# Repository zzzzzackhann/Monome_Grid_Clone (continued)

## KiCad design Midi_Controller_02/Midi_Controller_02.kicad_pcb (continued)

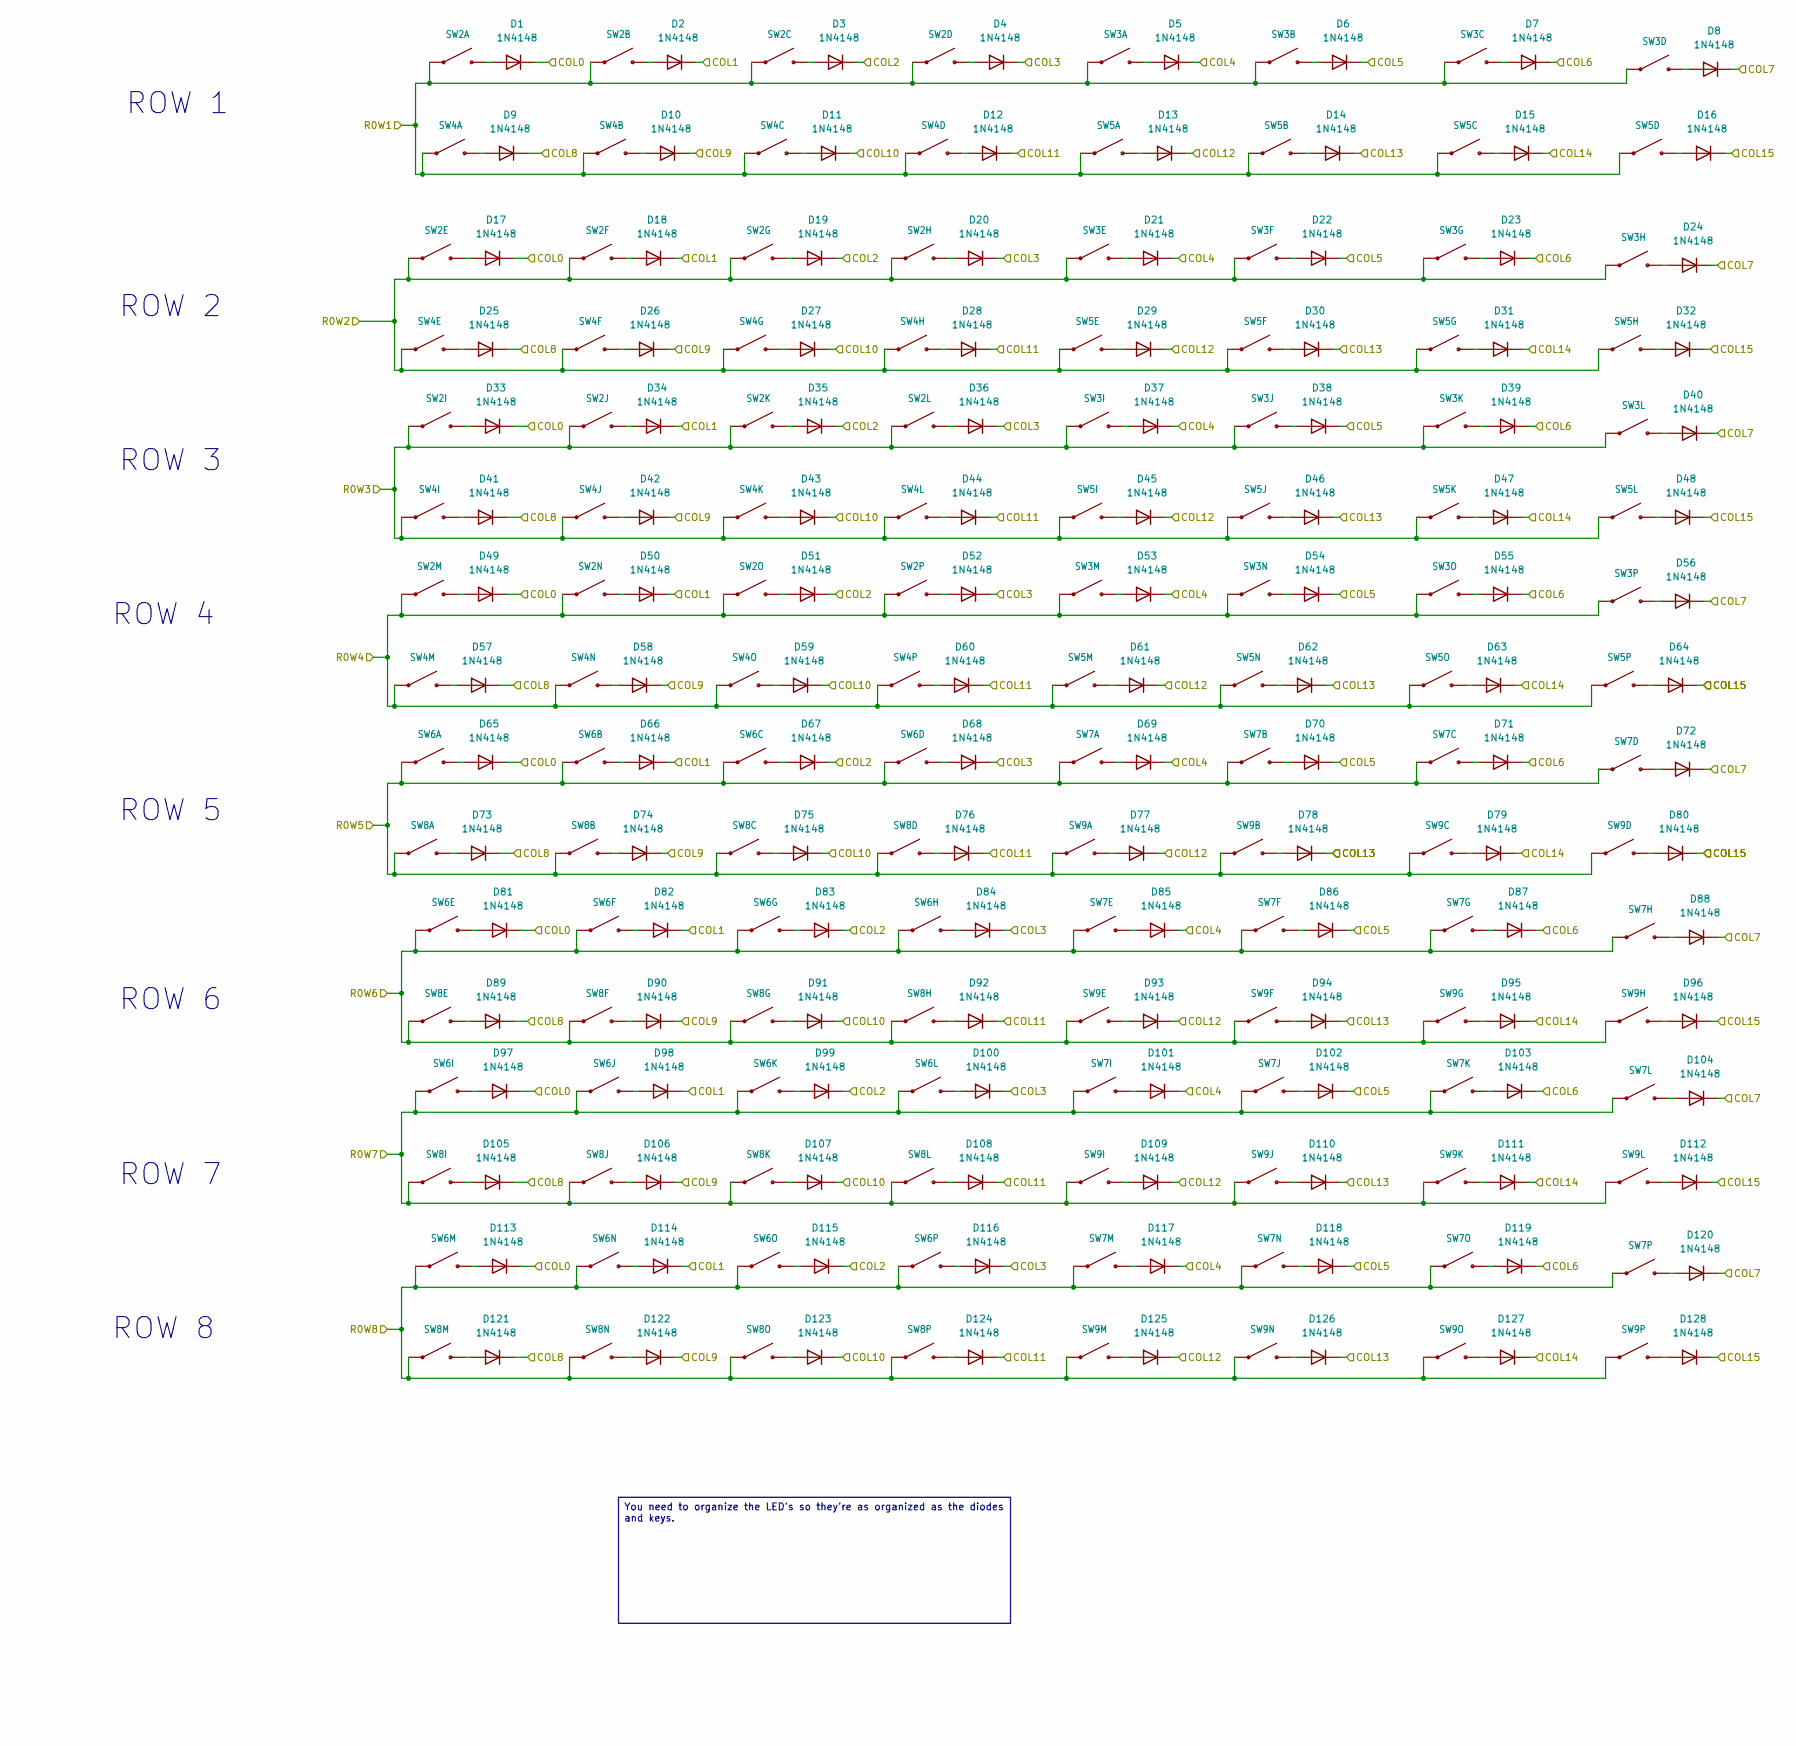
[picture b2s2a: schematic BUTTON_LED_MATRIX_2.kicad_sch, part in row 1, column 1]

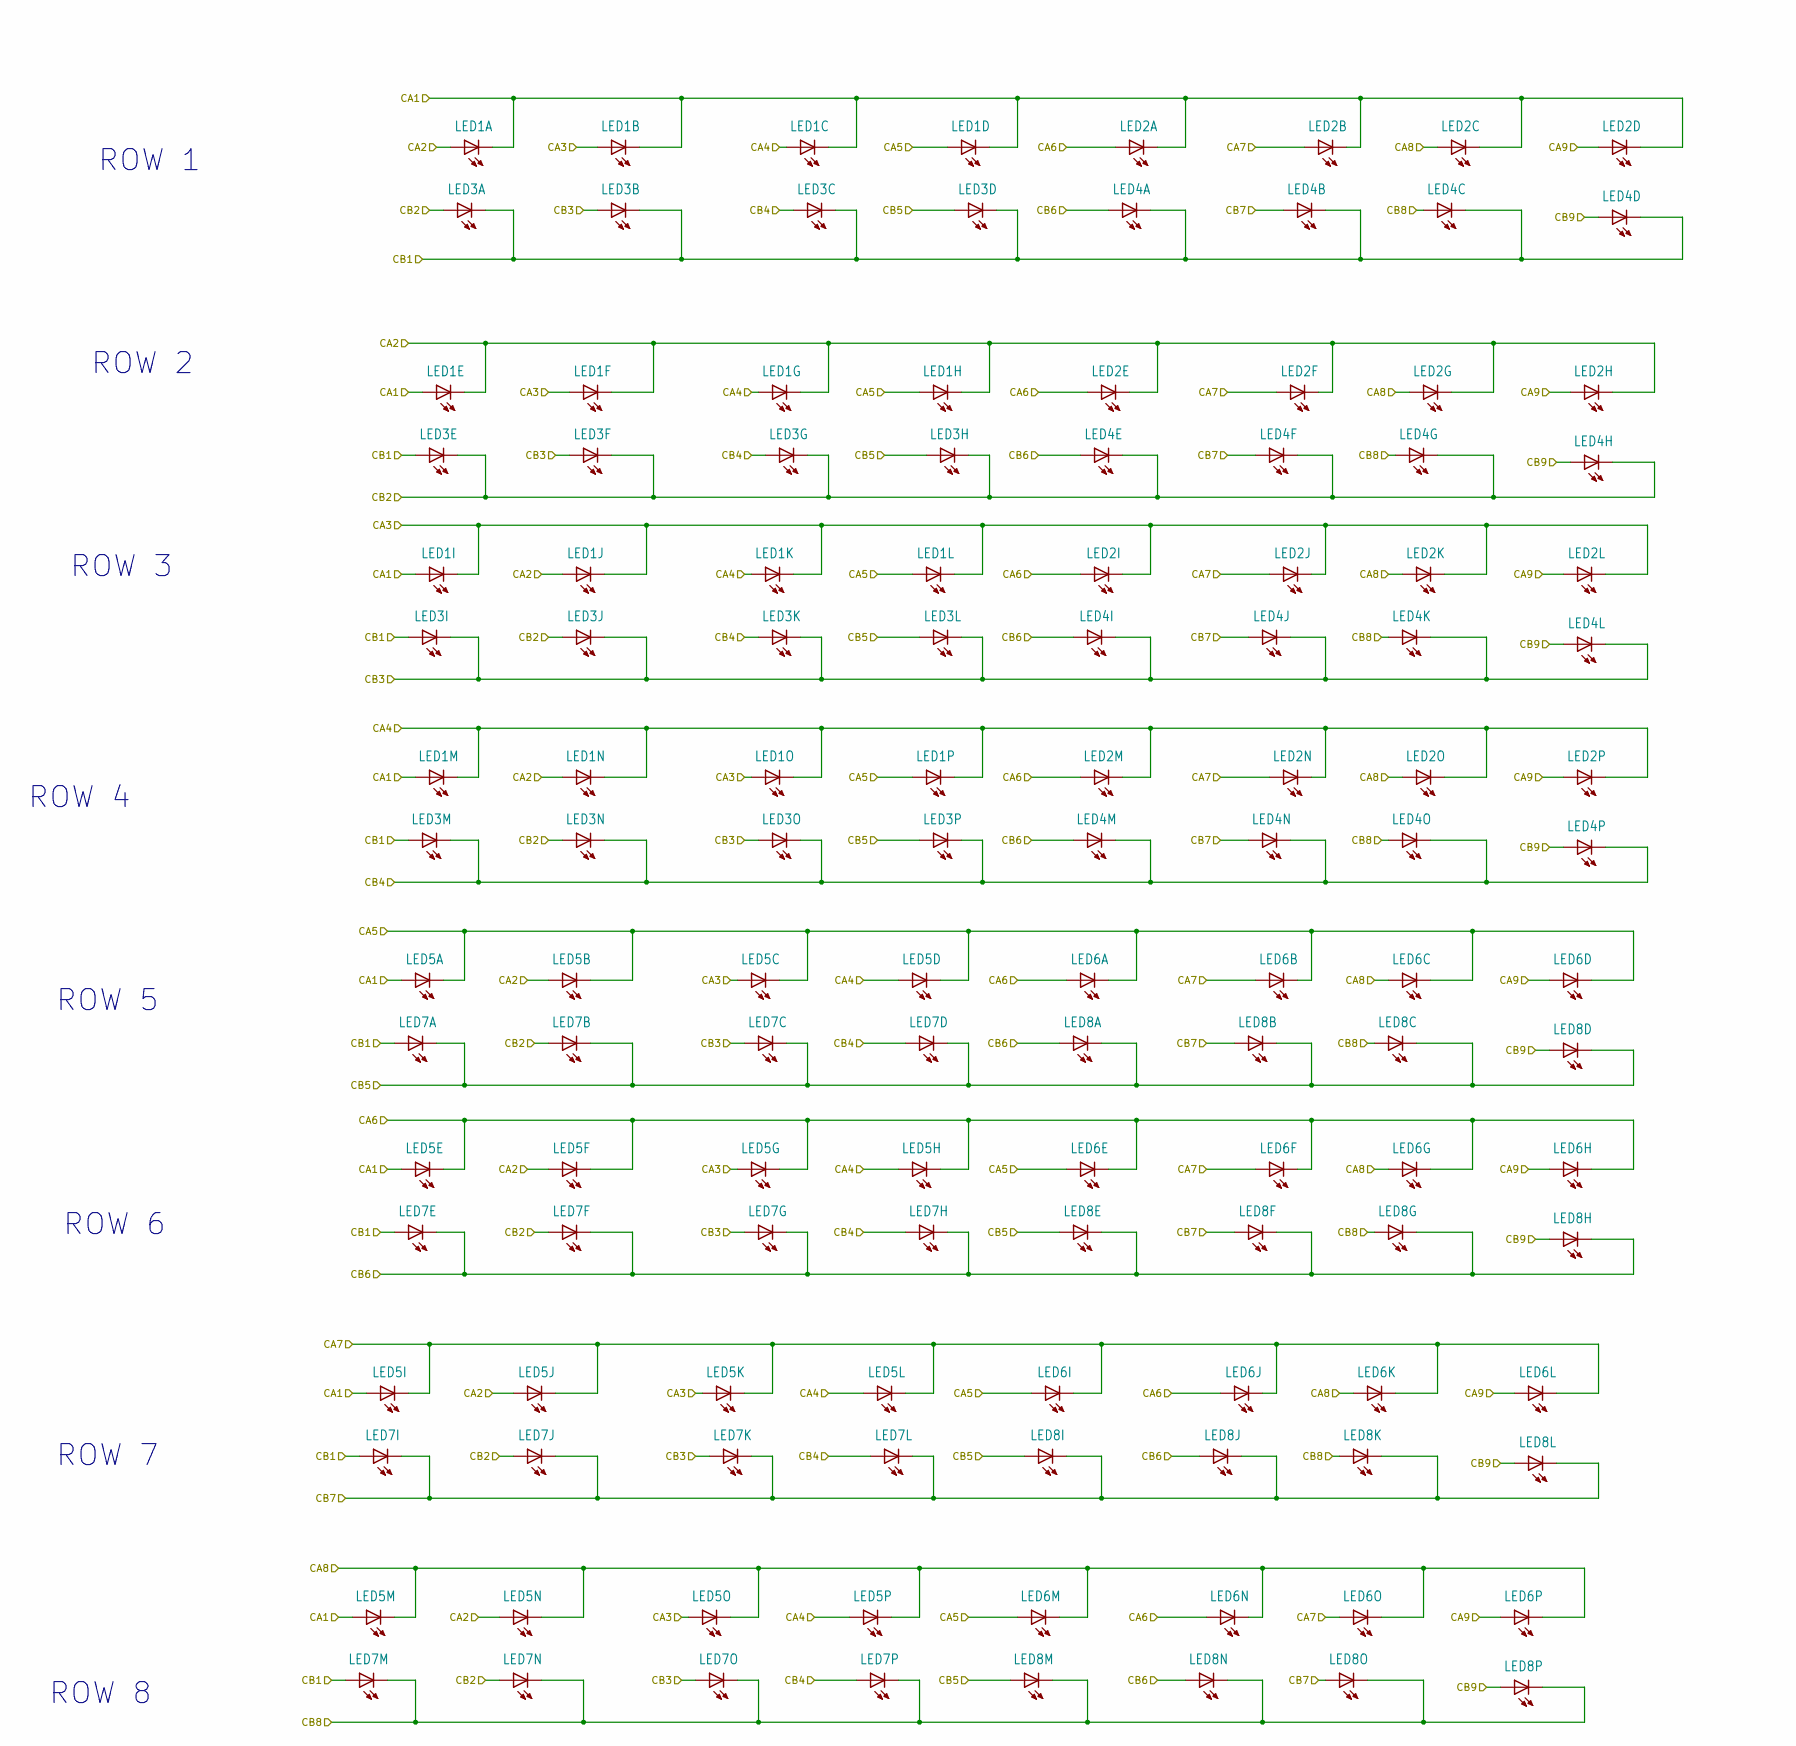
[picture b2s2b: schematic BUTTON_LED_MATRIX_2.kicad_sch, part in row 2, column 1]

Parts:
D1, D2, D3, D4, D5, D6, D7, D8, D9, D10, D11, D12, D13, D14, D15, D16, D17, D18, D19, D20, D21, D22, D23, D24, D25, D26, D27, D28, D29, D30, D31, D32, D33, D34, D35, D36, D37, D38, D39, D40, D41, D42, D43, D44, D45, D46, D47, D48, D49, D50, D51, D52, D53, D54, D55, D56, D57, D58, D59, D60, D61, D62, D63, D64, D65, D66, D67, D68, D69, D70, D71, D72, D73, D74, D75, D76, D77, D78, D79, D80, D81, D82, D83, D84, D85, D86, D87, D88, D89, D90, D91, D92, D93, D94, D95, D96, D97, D98, D99, D100, D101, D102, D103, D104, D105, D106, D107, D108, D109, D110, D111, D112, D113, D114, D115, D116, D117, D118, D119, D120, D121, D122, D123, D124, D125, D126, D127, D128: 1N4148; D_SOD-123
LED1, LED2, LED3, LED4, LED5, LED6, LED7, LED8: LED3MM-4X4GRID
SW2, SW3, SW4, SW5, SW6, SW7, SW8, SW9: ELAST_PAD_SQUARE_10MM_5.4MM_4X4GRID

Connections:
/CONTROLLER-MATRIX/CA1: LED1.A5 (A), LED1.A9 (A), LED1.A13 (A), LED1.K1 (C), LED1.K2 (C), LED1.K3 (C), LED1.K4 (C), LED2.K1 (C), LED2.K2 (C), LED2.K3 (C), LED2.K4 (C), LED5.A1 (A), LED5.A5 (A), LED5.A9 (A), LED5.A13 (A); also elsewhere on the board
/CONTROLLER-MATRIX/CA2: LED1.A1 (A), LED1.A10 (A), LED1.A14 (A), LED1.K5 (C), LED1.K6 (C), LED1.K7 (C), LED1.K8 (C), LED2.K5 (C), LED2.K6 (C), LED2.K7 (C), LED2.K8 (C), LED5.A2 (A), LED5.A6 (A), LED5.A10 (A), LED5.A14 (A); also elsewhere on the board
/CONTROLLER-MATRIX/CA3: LED1.A2 (A), LED1.A6 (A), LED1.A15 (A), LED1.K9 (C), LED1.K10 (C), LED1.K11 (C), LED1.K12 (C), LED2.K9 (C), LED2.K10 (C), LED2.K11 (C), LED2.K12 (C), LED5.A3 (A), LED5.A7 (A), LED5.A11 (A), LED5.A15 (A); also elsewhere on the board
/CONTROLLER-MATRIX/CA4: LED1.A3 (A), LED1.A7 (A), LED1.A11 (A), LED1.K13 (C), LED1.K14 (C), LED1.K15 (C), LED1.K16 (C), LED2.K13 (C), LED2.K14 (C), LED2.K15 (C), LED2.K16 (C), LED5.A4 (A), LED5.A8 (A), LED5.A12 (A), LED5.A16 (A); also elsewhere on the board
/CONTROLLER-MATRIX/CA5: LED1.A4 (A), LED1.A8 (A), LED1.A12 (A), LED1.A16 (A), LED5.K1 (C), LED5.K2 (C), LED5.K3 (C), LED5.K4 (C), LED6.A5 (A), LED6.A9 (A), LED6.A13 (A), LED6.K1 (C), LED6.K2 (C), LED6.K3 (C), LED6.K4 (C); also elsewhere on the board
/CONTROLLER-MATRIX/CA6: LED2.A1 (A), LED2.A5 (A), LED2.A9 (A), LED2.A13 (A), LED5.K5 (C), LED5.K6 (C), LED5.K7 (C), LED5.K8 (C), LED6.A1 (A), LED6.A10 (A), LED6.A14 (A), LED6.K5 (C), LED6.K6 (C), LED6.K7 (C), LED6.K8 (C); also elsewhere on the board
/CONTROLLER-MATRIX/CA7: LED2.A2 (A), LED2.A6 (A), LED2.A10 (A), LED2.A14 (A), LED5.K9 (C), LED5.K10 (C), LED5.K11 (C), LED5.K12 (C), LED6.A2 (A), LED6.A6 (A), LED6.A15 (A), LED6.K9 (C), LED6.K10 (C), LED6.K11 (C), LED6.K12 (C); also elsewhere on the board
/CONTROLLER-MATRIX/CA8: LED2.A3 (A), LED2.A7 (A), LED2.A11 (A), LED2.A15 (A), LED5.K13 (C), LED5.K14 (C), LED5.K15 (C), LED5.K16 (C), LED6.A3 (A), LED6.A7 (A), LED6.A11 (A), LED6.K13 (C), LED6.K14 (C), LED6.K15 (C), LED6.K16 (C); also elsewhere on the board
/CONTROLLER-MATRIX/CA9: LED2.A4 (A), LED2.A8 (A), LED2.A12 (A), LED2.A16 (A), LED6.A4 (A), LED6.A8 (A), LED6.A12 (A), LED6.A16 (A); also elsewhere on the board
/CONTROLLER-MATRIX/CB1: LED3.A5 (A), LED3.A9 (A), LED3.A13 (A), LED3.K1 (C), LED3.K2 (C), LED3.K3 (C), LED3.K4 (C), LED4.K1 (C), LED4.K2 (C), LED4.K3 (C), LED4.K4 (C), LED7.A1 (A), LED7.A5 (A), LED7.A9 (A), LED7.A13 (A); also elsewhere on the board
/CONTROLLER-MATRIX/CB2: LED3.A1 (A), LED3.A10 (A), LED3.A14 (A), LED3.K5 (C), LED3.K6 (C), LED3.K7 (C), LED3.K8 (C), LED4.K5 (C), LED4.K6 (C), LED4.K7 (C), LED4.K8 (C), LED7.A2 (A), LED7.A6 (A), LED7.A10 (A), LED7.A14 (A); also elsewhere on the board
/CONTROLLER-MATRIX/CB3: LED3.A2 (A), LED3.A6 (A), LED3.A15 (A), LED3.K9 (C), LED3.K10 (C), LED3.K11 (C), LED3.K12 (C), LED4.K9 (C), LED4.K10 (C), LED4.K11 (C), LED4.K12 (C), LED7.A3 (A), LED7.A7 (A), LED7.A11 (A), LED7.A15 (A); also elsewhere on the board
/CONTROLLER-MATRIX/CB4: LED3.A3 (A), LED3.A7 (A), LED3.A11 (A), LED3.K13 (C), LED3.K14 (C), LED3.K15 (C), LED3.K16 (C), LED4.K13 (C), LED4.K14 (C), LED4.K15 (C), LED4.K16 (C), LED7.A4 (A), LED7.A8 (A), LED7.A12 (A), LED7.A16 (A); also elsewhere on the board
/CONTROLLER-MATRIX/CB5: LED3.A4 (A), LED3.A8 (A), LED3.A12 (A), LED3.A16 (A), LED7.K1 (C), LED7.K2 (C), LED7.K3 (C), LED7.K4 (C), LED8.A5 (A), LED8.A9 (A), LED8.A13 (A), LED8.K1 (C), LED8.K2 (C), LED8.K3 (C), LED8.K4 (C); also elsewhere on the board
/CONTROLLER-MATRIX/CB6: LED4.A1 (A), LED4.A5 (A), LED4.A9 (A), LED4.A13 (A), LED7.K5 (C), LED7.K6 (C), LED7.K7 (C), LED7.K8 (C), LED8.A1 (A), LED8.A10 (A), LED8.A14 (A), LED8.K5 (C), LED8.K6 (C), LED8.K7 (C), LED8.K8 (C); also elsewhere on the board
/CONTROLLER-MATRIX/CB7: LED4.A2 (A), LED4.A6 (A), LED4.A10 (A), LED4.A14 (A), LED7.K9 (C), LED7.K10 (C), LED7.K11 (C), LED7.K12 (C), LED8.A2 (A), LED8.A6 (A), LED8.A15 (A), LED8.K9 (C), LED8.K10 (C), LED8.K11 (C), LED8.K12 (C); also elsewhere on the board
/CONTROLLER-MATRIX/CB8: LED4.A3 (A), LED4.A7 (A), LED4.A11 (A), LED4.A15 (A), LED7.K13 (C), LED7.K14 (C), LED7.K15 (C), LED7.K16 (C), LED8.A3 (A), LED8.A7 (A), LED8.A11 (A), LED8.K13 (C), LED8.K14 (C), LED8.K15 (C), LED8.K16 (C); also elsewhere on the board
/CONTROLLER-MATRIX/CB9: LED4.A4 (A), LED4.A8 (A), LED4.A12 (A), LED4.A16 (A), LED8.A4 (A), LED8.A8 (A), LED8.A12 (A), LED8.A16 (A); also elsewhere on the board
/CONTROLLER-MATRIX/COL0: D1.1 (K), D17.1 (K), D33.1 (K), D49.1 (K), D65.1 (K), D81.1 (K), D97.1 (K), D113.1 (K); also elsewhere on the board
/CONTROLLER-MATRIX/COL1: D2.1 (K), D18.1 (K), D34.1 (K), D50.1 (K), D66.1 (K), D82.1 (K), D98.1 (K), D114.1 (K); also elsewhere on the board
/CONTROLLER-MATRIX/COL2: D3.1 (K), D19.1 (K), D35.1 (K), D51.1 (K), D67.1 (K), D83.1 (K), D99.1 (K), D115.1 (K); also elsewhere on the board
/CONTROLLER-MATRIX/COL3: D4.1 (K), D20.1 (K), D36.1 (K), D52.1 (K), D68.1 (K), D84.1 (K), D100.1 (K), D116.1 (K); also elsewhere on the board
/CONTROLLER-MATRIX/COL4: D5.1 (K), D21.1 (K), D37.1 (K), D53.1 (K), D69.1 (K), D85.1 (K), D101.1 (K), D117.1 (K); also elsewhere on the board
/CONTROLLER-MATRIX/COL5: D6.1 (K), D22.1 (K), D38.1 (K), D54.1 (K), D70.1 (K), D86.1 (K), D102.1 (K), D118.1 (K); also elsewhere on the board
/CONTROLLER-MATRIX/COL6: D7.1 (K), D23.1 (K), D39.1 (K), D55.1 (K), D71.1 (K), D87.1 (K), D103.1 (K), D119.1 (K); also elsewhere on the board
/CONTROLLER-MATRIX/COL7: D8.1 (K), D24.1 (K), D40.1 (K), D56.1 (K), D72.1 (K), D88.1 (K), D104.1 (K), D120.1 (K); also elsewhere on the board
/CONTROLLER-MATRIX/COL8: D9.1 (K), D25.1 (K), D41.1 (K), D57.1 (K), D73.1 (K), D89.1 (K), D105.1 (K), D121.1 (K); also elsewhere on the board
/CONTROLLER-MATRIX/COL9: D10.1 (K), D26.1 (K), D42.1 (K), D58.1 (K), D74.1 (K), D90.1 (K), D106.1 (K), D122.1 (K); also elsewhere on the board
/CONTROLLER-MATRIX/COL10: D11.1 (K), D27.1 (K), D43.1 (K), D59.1 (K), D75.1 (K), D91.1 (K), D107.1 (K), D123.1 (K); also elsewhere on the board
/CONTROLLER-MATRIX/COL11: D12.1 (K), D28.1 (K), D44.1 (K), D60.1 (K), D76.1 (K), D92.1 (K), D108.1 (K), D124.1 (K); also elsewhere on the board
/CONTROLLER-MATRIX/COL12: D13.1 (K), D29.1 (K), D45.1 (K), D61.1 (K), D77.1 (K), D93.1 (K), D109.1 (K), D125.1 (K); also elsewhere on the board
/CONTROLLER-MATRIX/COL13: D14.1 (K), D30.1 (K), D46.1 (K), D62.1 (K), D78.1 (K), D94.1 (K), D110.1 (K), D126.1 (K); also elsewhere on the board
/CONTROLLER-MATRIX/COL14: D15.1 (K), D31.1 (K), D47.1 (K), D63.1 (K), D79.1 (K), D95.1 (K), D111.1 (K), D127.1 (K); also elsewhere on the board
/CONTROLLER-MATRIX/COL15: D16.1 (K), D32.1 (K), D48.1 (K), D64.1 (K), D80.1 (K), D96.1 (K), D112.1 (K), D128.1 (K); also elsewhere on the board
/CONTROLLER-MATRIX/ROW1: SW2.A1, SW2.A2, SW2.A3, SW2.A4, SW3.A1, SW3.A2, SW3.A3, SW3.A4, SW4.A1, SW4.A2, SW4.A3, SW4.A4, SW5.A1, SW5.A2, SW5.A3, SW5.A4
/CONTROLLER-MATRIX/ROW2: SW2.A5, SW2.A6, SW2.A7, SW2.A8, SW3.A5, SW3.A6, SW3.A7, SW3.A8, SW4.A5, SW4.A6, SW4.A7, SW4.A8, SW5.A5, SW5.A6, SW5.A7, SW5.A8
/CONTROLLER-MATRIX/ROW3: SW2.A9, SW2.A10, SW2.A11, SW2.A12, SW3.A9, SW3.A10, SW3.A11, SW3.A12, SW4.A9, SW4.A10, SW4.A11, SW4.A12, SW5.A9, SW5.A10, SW5.A11, SW5.A12
/CONTROLLER-MATRIX/ROW4: SW2.A13, SW2.A14, SW2.A15, SW2.A16, SW3.A13, SW3.A14, SW3.A15, SW3.A16, SW4.A13, SW4.A14, SW4.A15, SW4.A16, SW5.A13, SW5.A14, SW5.A15, SW5.A16
/CONTROLLER-MATRIX/ROW5: SW6.A1, SW6.A2, SW6.A3, SW6.A4, SW7.A1, SW7.A2, SW7.A3, SW7.A4, SW8.A1, SW8.A2, SW8.A3, SW8.A4, SW9.A1, SW9.A2, SW9.A3, SW9.A4
/CONTROLLER-MATRIX/ROW6: SW6.A5, SW6.A6, SW6.A7, SW6.A8, SW7.A5, SW7.A6, SW7.A7, SW7.A8, SW8.A5, SW8.A6, SW8.A7, SW8.A8, SW9.A5, SW9.A6, SW9.A7, SW9.A8
/CONTROLLER-MATRIX/ROW7: SW6.A9, SW6.A10, SW6.A11, SW6.A12, SW7.A9, SW7.A10, SW7.A11, SW7.A12, SW8.A9, SW8.A10, SW8.A11, SW8.A12, SW9.A9, SW9.A10, SW9.A11, SW9.A12
/CONTROLLER-MATRIX/ROW8: SW6.A13, SW6.A14, SW6.A15, SW6.A16, SW7.A13, SW7.A14, SW7.A15, SW7.A16, SW8.A13, SW8.A14, SW8.A15, SW8.A16, SW9.A13, SW9.A14, SW9.A15, SW9.A16
unnamed: D1.2 (A), SW2.B1
unnamed: D2.2 (A), SW2.B2
unnamed: D3.2 (A), SW2.B3
unnamed: D4.2 (A), SW2.B4
unnamed: D5.2 (A), SW3.B1
unnamed: D6.2 (A), SW3.B2
unnamed: D7.2 (A), SW3.B3
unnamed: D8.2 (A), SW3.B4
unnamed: D9.2 (A), SW4.B1
unnamed: D10.2 (A), SW4.B2
unnamed: D11.2 (A), SW4.B3
unnamed: D12.2 (A), SW4.B4
unnamed: D13.2 (A), SW5.B1
unnamed: D14.2 (A), SW5.B2
unnamed: D15.2 (A), SW5.B3
unnamed: D16.2 (A), SW5.B4
unnamed: D17.2 (A), SW2.B5
unnamed: D18.2 (A), SW2.B6
unnamed: D19.2 (A), SW2.B7
unnamed: D20.2 (A), SW2.B8
unnamed: D21.2 (A), SW3.B5
unnamed: D22.2 (A), SW3.B6
unnamed: D23.2 (A), SW3.B7
unnamed: D24.2 (A), SW3.B8
unnamed: D25.2 (A), SW4.B5
unnamed: D26.2 (A), SW4.B6
unnamed: D27.2 (A), SW4.B7
unnamed: D28.2 (A), SW4.B8
unnamed: D29.2 (A), SW5.B5
unnamed: D30.2 (A), SW5.B6
unnamed: D31.2 (A), SW5.B7
unnamed: D32.2 (A), SW5.B8
unnamed: D33.2 (A), SW2.B9
unnamed: D34.2 (A), SW2.B10
unnamed: D35.2 (A), SW2.B11
unnamed: D36.2 (A), SW2.B12
unnamed: D37.2 (A), SW3.B9
unnamed: D38.2 (A), SW3.B10
unnamed: D39.2 (A), SW3.B11
unnamed: D40.2 (A), SW3.B12
unnamed: D41.2 (A), SW4.B9
unnamed: D42.2 (A), SW4.B10
unnamed: D43.2 (A), SW4.B11
unnamed: D44.2 (A), SW4.B12
unnamed: D45.2 (A), SW5.B9
unnamed: D46.2 (A), SW5.B10
unnamed: D47.2 (A), SW5.B11
unnamed: D48.2 (A), SW5.B12
unnamed: D49.2 (A), SW2.B13
unnamed: D50.2 (A), SW2.B14
unnamed: D51.2 (A), SW2.B15
unnamed: D52.2 (A), SW2.B16
unnamed: D53.2 (A), SW3.B13
unnamed: D54.2 (A), SW3.B14
unnamed: D55.2 (A), SW3.B15
unnamed: D56.2 (A), SW3.B16
unnamed: D57.2 (A), SW4.B13
unnamed: D58.2 (A), SW4.B14
unnamed: D59.2 (A), SW4.B15
unnamed: D60.2 (A), SW4.B16
unnamed: D61.2 (A), SW5.B13
unnamed: D62.2 (A), SW5.B14
unnamed: D63.2 (A), SW5.B15
unnamed: D64.2 (A), SW5.B16
unnamed: D65.2 (A), SW6.B1
unnamed: D66.2 (A), SW6.B2
unnamed: D67.2 (A), SW6.B3
unnamed: D68.2 (A), SW6.B4
unnamed: D69.2 (A), SW7.B1
unnamed: D70.2 (A), SW7.B2
unnamed: D71.2 (A), SW7.B3
unnamed: D72.2 (A), SW7.B4
unnamed: D73.2 (A), SW8.B1
unnamed: D74.2 (A), SW8.B2
unnamed: D75.2 (A), SW8.B3
unnamed: D76.2 (A), SW8.B4
unnamed: D77.2 (A), SW9.B1
unnamed: D78.2 (A), SW9.B2
unnamed: D79.2 (A), SW9.B3
unnamed: D80.2 (A), SW9.B4
unnamed: D81.2 (A), SW6.B5
unnamed: D82.2 (A), SW6.B6
unnamed: D83.2 (A), SW6.B7
unnamed: D84.2 (A), SW6.B8
unnamed: D85.2 (A), SW7.B5
unnamed: D86.2 (A), SW7.B6
unnamed: D87.2 (A), SW7.B7
unnamed: D88.2 (A), SW7.B8
unnamed: D89.2 (A), SW8.B5
unnamed: D90.2 (A), SW8.B6
unnamed: D91.2 (A), SW8.B7
unnamed: D92.2 (A), SW8.B8
unnamed: D93.2 (A), SW9.B5
unnamed: D94.2 (A), SW9.B6
unnamed: D95.2 (A), SW9.B7
unnamed: D96.2 (A), SW9.B8
unnamed: D97.2 (A), SW6.B9
unnamed: D98.2 (A), SW6.B10
unnamed: D99.2 (A), SW6.B11
unnamed: D100.2 (A), SW6.B12
unnamed: D101.2 (A), SW7.B9
unnamed: D102.2 (A), SW7.B10
unnamed: D103.2 (A), SW7.B11
unnamed: D104.2 (A), SW7.B12
unnamed: D105.2 (A), SW8.B9
unnamed: D106.2 (A), SW8.B10
unnamed: D107.2 (A), SW8.B11
unnamed: D108.2 (A), SW8.B12
unnamed: D109.2 (A), SW9.B9
unnamed: D110.2 (A), SW9.B10
unnamed: D111.2 (A), SW9.B11
unnamed: D112.2 (A), SW9.B12
unnamed: D113.2 (A), SW6.B13
unnamed: D114.2 (A), SW6.B14
unnamed: D115.2 (A), SW6.B15
unnamed: D116.2 (A), SW6.B16
unnamed: D117.2 (A), SW7.B13
unnamed: D118.2 (A), SW7.B14
unnamed: D119.2 (A), SW7.B15
unnamed: D120.2 (A), SW7.B16
unnamed: D121.2 (A), SW8.B13
unnamed: D122.2 (A), SW8.B14
unnamed: D123.2 (A), SW8.B15
unnamed: D124.2 (A), SW8.B16
unnamed: D125.2 (A), SW9.B13
unnamed: D126.2 (A), SW9.B14
unnamed: D127.2 (A), SW9.B15
unnamed: D128.2 (A), SW9.B16

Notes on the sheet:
ROW 7
ROW 6
ROW 3
ROW 2
ROW 8
ROW 4
ROW 5
ROW 1
You need to organize the LED's so they're as organized as the diodes and keys.

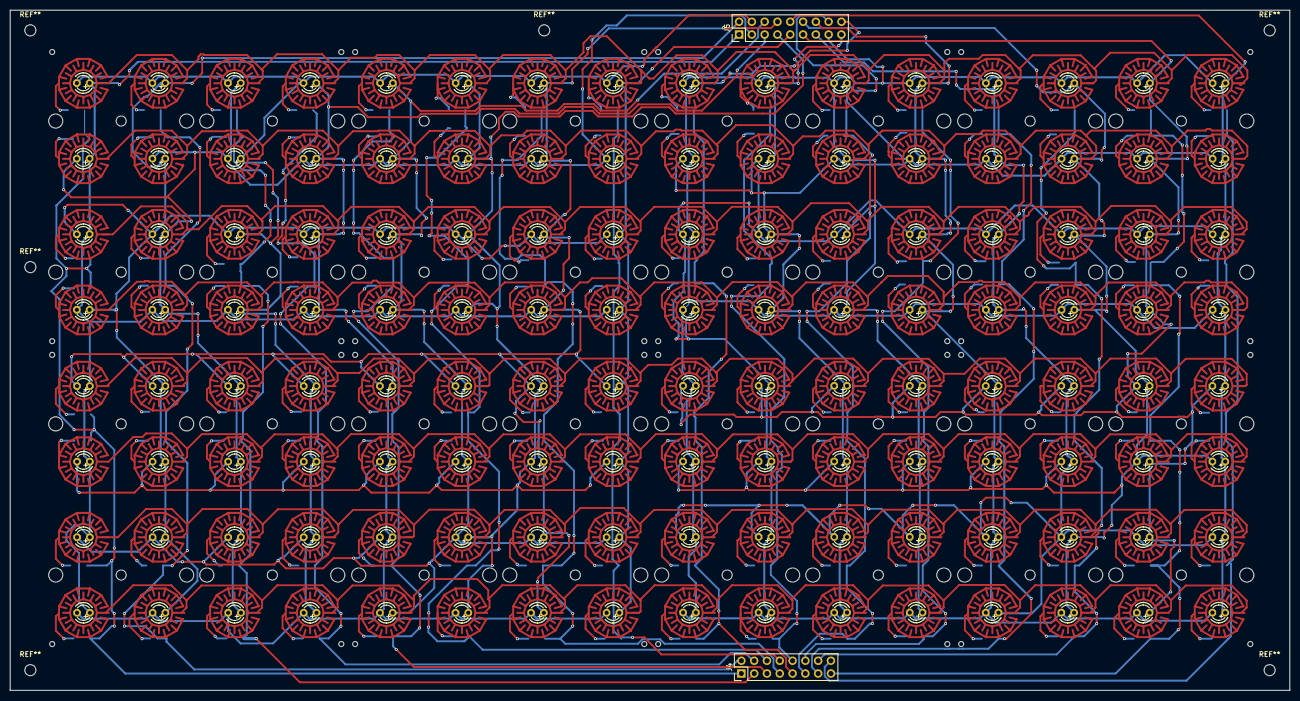
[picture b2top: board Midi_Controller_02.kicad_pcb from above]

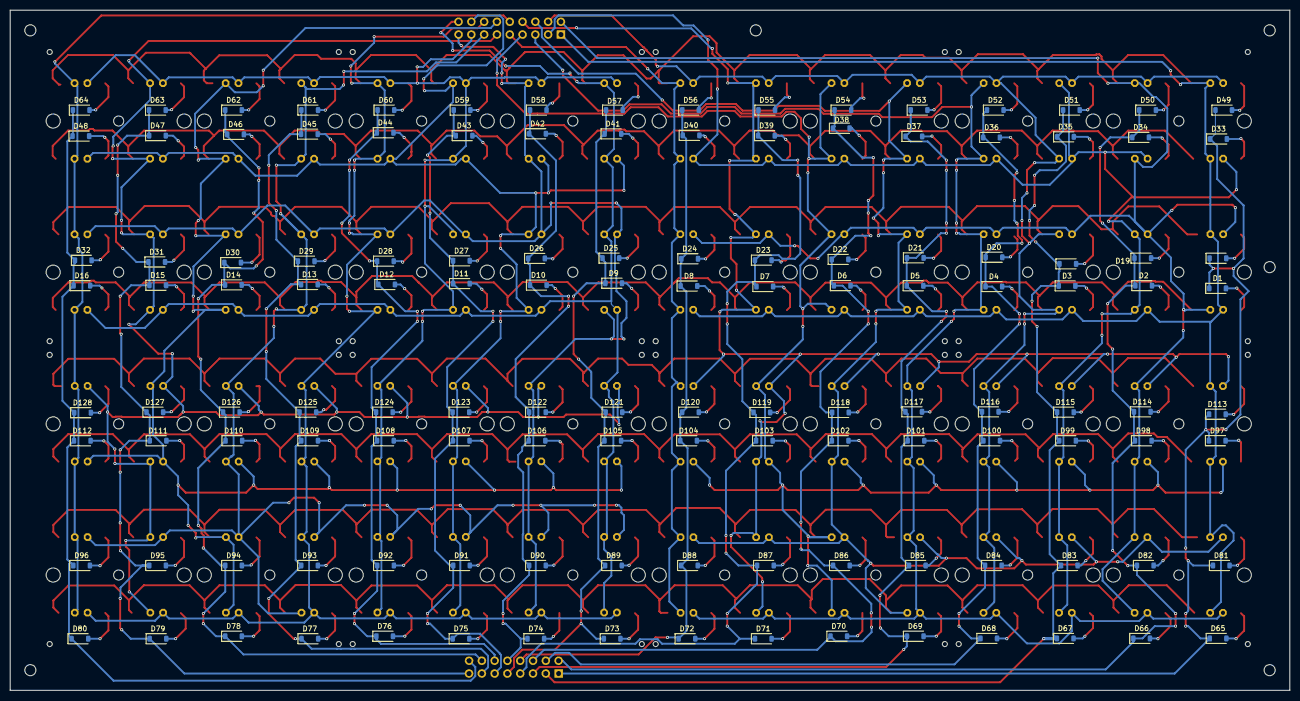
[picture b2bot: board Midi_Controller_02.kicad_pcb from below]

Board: 2 copper layers, 254.0 x 135.0 mm, 146 parts (128 on the bottom side), 170 nets.

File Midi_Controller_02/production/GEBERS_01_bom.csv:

Designator,Footprint,Quantity,Value,LCSC Part #
"D1, D10, D100, D101, D102, D103, D104, D105, D106, D107, D108, D109, D11, D110, D111, D112, D113, D114, D115, D116, D117, D118, D119, D12, D120, D121, D122, D123, D124, D125, D126, D127, D128, D13, D14, D15, D16, D17, D18, D19, D2, D20, D21, D22, D23, D24, D25, D26, D27, D28, D29, D3, D30, D31, D32, D33, D34, D35, D36, D37, D38, D39, D4, D40, D41, D42, D43, D44, D45, D46, D47, D48, D49, D5, D50, D51, D52, D53, D54, D55, D56, D57, D58, D59, D6, D60, D61, D62, D63, D64, D65, D66, D67, D68, D69, D7, D70, D71, D72, D73, D74, D75, D76, D77, D78, D79, D8, D80, D81, D82, D83, D84, D85, D86, D87, D88, D89, D9, D90, D91, D92, D93, D94, D95, D96, D97, D98, D99",D_SOD-123,128,1N4148,
J4,PinHeader_2x08_P2.54mm_Vertical,1,COL HEADER,
J5,PinHeader_2x09_P2.54mm_Vertical,1,CA HEADER,
"LED1, LED2, LED3, LED4, LED5, LED6, LED7, LED8",LED3MM-4X4GRID,8,~,
"SW2, SW3, SW4, SW5, SW6, SW7, SW8, SW9",ELAST_PAD_SQUARE_10MM_5.4MM_4X4GRID,8,~,

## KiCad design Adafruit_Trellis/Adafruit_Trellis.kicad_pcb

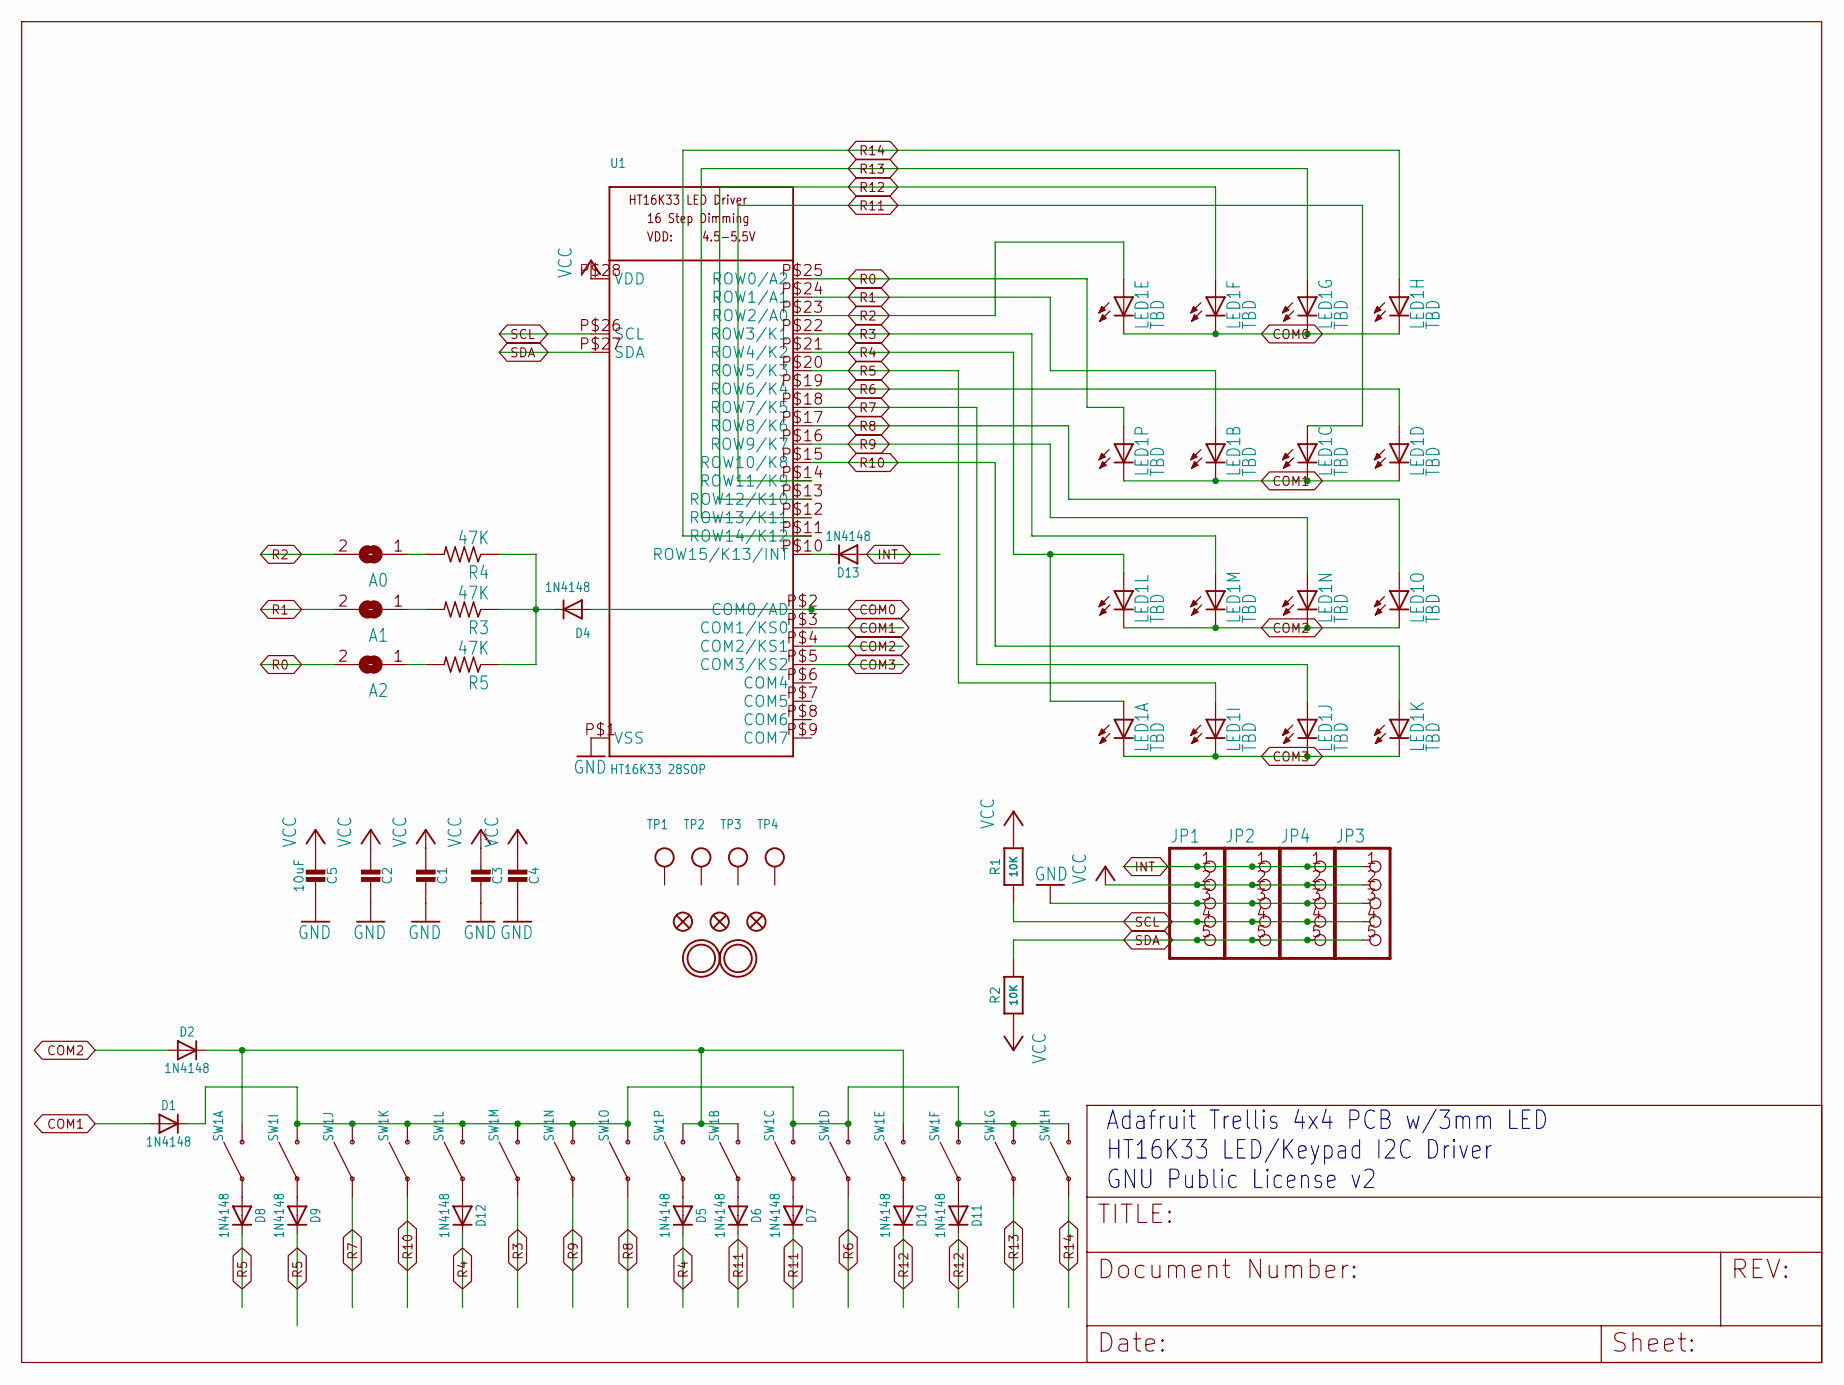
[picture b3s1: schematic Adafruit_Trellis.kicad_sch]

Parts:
A0, A1, A2: SOLDERJUMPERREFLOW_NOPASTE; SOLDERJUMPER_REFLOW_NOPASTE
C1, C2, C3, C4: CAP_CERAMIC_0805; _0805
C5: 10uF; _0805
D1, D2, D5, D6, D7, D8, D9, D10, D11, D12, D13: 1N4148; SOD-323
D4: 1N4148; SOD-323F
FID1, FID2, FID3: FIDUCIAL""; FIDUCIAL_1MM
JP1, JP2, JP3, JP4: HEADER-1X5EDGESMT; 1X5_SMT
LED1: TBD; LED3MM-4X4GRID
R1, R2: 10K; _0805
R3, R4, R5: 47K; R0805
SW1: SWITCH-SILICON-4X4GRID-10MM-5.4MM; ELAST_PAD_SQUARE_10MM_5.4MM_4X4GRID
TP1, TP2, TP3, TP4: TESTPOINT; TESTPOINT_SMT
U1: HT16K33 28SOP; SOP28_300MIL
U$1, U$2: MOUNTINGHOLE2.5; MOUNTINGHOLE_2.5_PLATED

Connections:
COM0: D4.A, LED1.K13 (C), LED1.K14 (C), LED1.K15 (C), LED1.K16 (C), U1.P$2 (COM0/AD)
COM1: D1.A, LED1.K9 (C), LED1.K10 (C), LED1.K11 (C), LED1.K12 (C), U1.P$3 (COM1/KS0)
COM2: D2.A, LED1.K5 (C), LED1.K6 (C), LED1.K7 (C), LED1.K8 (C), U1.P$4 (COM2/KS1)
COM3: LED1.K1 (C), LED1.K2 (C), LED1.K3 (C), LED1.K4 (C), U1.P$5 (COM3/KS2)
GND: C1.1, C2.1, C3.1, C4.1, C5.1, JP1.3, JP2.3, JP3.3, JP4.3, U1.P$1 (VSS)
INT: D13.A, JP1.1, JP2.1, JP3.1, JP4.1
unnamed: D2.C, SW1.B1, SW1.B9, SW1.B10, SW1.B13
unnamed: D13.C, U1.P$10 (ROW15/K13/INT)
unnamed: D5.A, SW1.A9
unnamed: D6.A, SW1.A10
unnamed: D1.C, SW1.B2, SW1.B3, SW1.B4, SW1.B5, SW1.B6, SW1.B7, SW1.B8, SW1.B11, SW1.B12, SW1.B14, SW1.B15, SW1.B16
unnamed: D7.A, SW1.A11
unnamed: D8.A, SW1.A1
unnamed: D9.A, SW1.A2
unnamed: A2.1, R5.2
unnamed: D10.A, SW1.A13
unnamed: D11.A, SW1.A14
unnamed: D12.A, SW1.A5
unnamed: D4.C, R3.1, R4.1, R5.1
unnamed: A1.1, R3.2
unnamed: A0.1, R4.2
R0: A2.2, LED1.A9 (A), U1.P$25 (ROW0/A2)
R1: A1.2, LED1.A10 (A), U1.P$24 (ROW1/A1)
R2: A0.2, LED1.A13 (A), U1.P$23 (ROW2/A0)
R3: LED1.A6 (A), SW1.A6, U1.P$22 (ROW3/K1)
R4: D5.C, D12.C, LED1.A1 (A), LED1.A5 (A), U1.P$21 (ROW4/K2)
R5: D8.C, D9.C, LED1.A2 (A), U1.P$20 (ROW5/K3)
R6: LED1.A12 (A), SW1.A12, U1.P$19 (ROW6/K4)
R7: LED1.A3 (A), SW1.A3, U1.P$18 (ROW7/K5)
R8: LED1.A8 (A), SW1.A8, U1.P$17 (ROW8/K6)
R9: LED1.A7 (A), SW1.A7, U1.P$16 (ROW9/K7)
R10: LED1.A4 (A), SW1.A4, U1.P$15 (ROW10/K8)
R11: D6.C, D7.C, LED1.A11 (A), U1.P$14 (ROW11/K9)
R12: D10.C, D11.C, LED1.A14 (A), U1.P$13 (ROW12/K10)
R13: LED1.A15 (A), SW1.A15, U1.P$12 (ROW13/K11)
R14: LED1.A16 (A), SW1.A16, U1.P$11 (ROW14/K12)
SCL: JP1.4, JP2.4, JP3.4, JP4.4, R1.1, U1.P$26 (SCL)
SDA: JP1.5, JP2.5, JP3.5, JP4.5, R2.2, U1.P$27 (SDA)
VCC: C1.2, C2.2, C3.2, C4.2, C5.2, JP1.2, JP2.2, JP3.2, JP4.2, R1.2, R2.1, U1.P$28 (VDD)

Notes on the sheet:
Adafruit Trellis 4x4 PCB w/3mm LED HT16K33 LED/Keypad I2C Driver GNU Public License v2
